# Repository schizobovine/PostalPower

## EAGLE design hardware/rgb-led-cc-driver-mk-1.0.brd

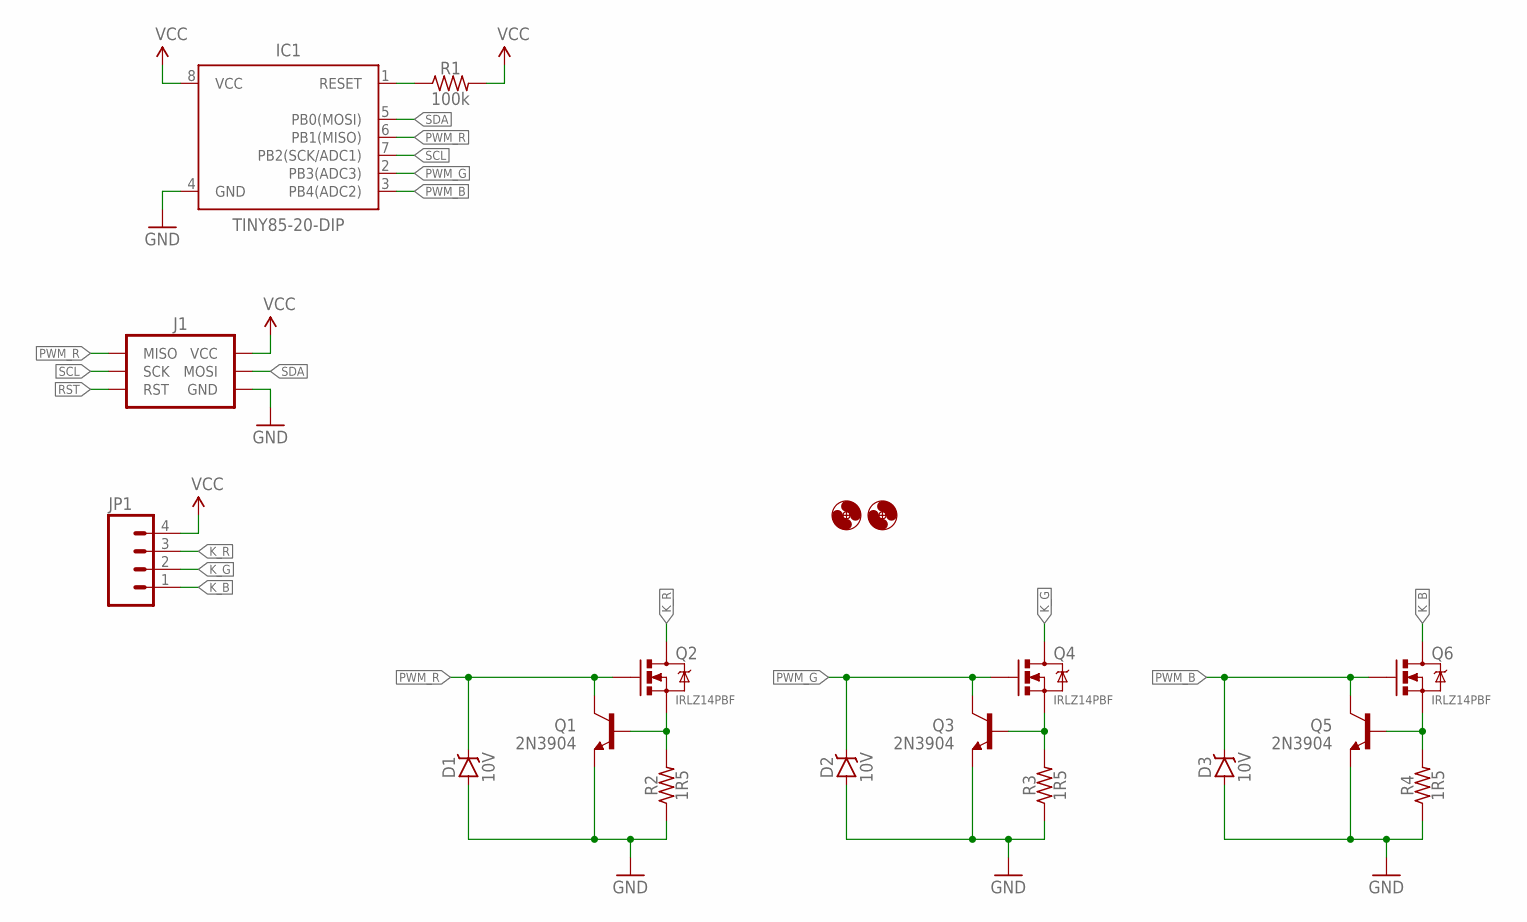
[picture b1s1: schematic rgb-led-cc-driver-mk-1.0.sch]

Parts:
D1, D2, D3: 10V; DIODE-7.62MM
H1, H2: HOLE#2; HOLE-#2
IC1: TINY85-20-DIP; DIP08
J1: AVR_SPI_PRG_6PTH_INLINE_I2C; AVR_ISP_INLINE_PTH_I2C
JP1: M04PTH; 1X04-PTH-VERT
Q1, Q3, Q5: 2N3904; TO-92-AMMO
Q2, Q4, Q6: IRLZ14PBF; TO220-THERMPAD
R1: 100k; RESISTOR-AXIAL-PTH-6.35MM
R2, R3, R4: 1R5; RESISTOR-AXIAL-PTH-10.16MM

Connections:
GND: D1.A, D2.A, D3.A, IC1.4 (GND), J1.GND, Q1.1 (E), Q3.1 (E), Q5.1 (E), R2.P$1 (1), R3.P$1 (1), R4.P$1 (1)
K_B: JP1.1, Q6.2@1 (D), Q6.2@2 (D)
K_G: JP1.2, Q4.2@1 (D), Q4.2@2 (D)
K_R: JP1.3, Q2.2@1 (D), Q2.2@2 (D)
unnamed: Q1.2 (B), Q2.3 (S), R2.P$2 (2)
unnamed: Q3.2 (B), Q4.3 (S), R3.P$2 (2)
unnamed: Q5.2 (B), Q6.3 (S), R4.P$2 (2)
PWM_B: D3.K (C), IC1.3 (PB4(ADC2)), Q5.3 (C), Q6.1 (G)
PWM_G: D2.K (C), IC1.2 (PB3(ADC3)), Q3.3 (C), Q4.1 (G)
PWM_R: D1.K (C), IC1.6 (PB1(MISO)), J1.MISO, Q1.3 (C), Q2.1 (G)
RST: IC1.1 (RESET), J1.RESET (RST), R1.P$1 (1)
SCL: IC1.7 (PB2(SCK/ADC1)), J1.SCK
SDA: IC1.5 (PB0(MOSI)), J1.MOSI
VCC: IC1.8 (VCC), J1.VCC, JP1.4, R1.P$2 (2)

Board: 2 copper layers, 18 parts (0 on the bottom side), 14 nets, no tracks yet.

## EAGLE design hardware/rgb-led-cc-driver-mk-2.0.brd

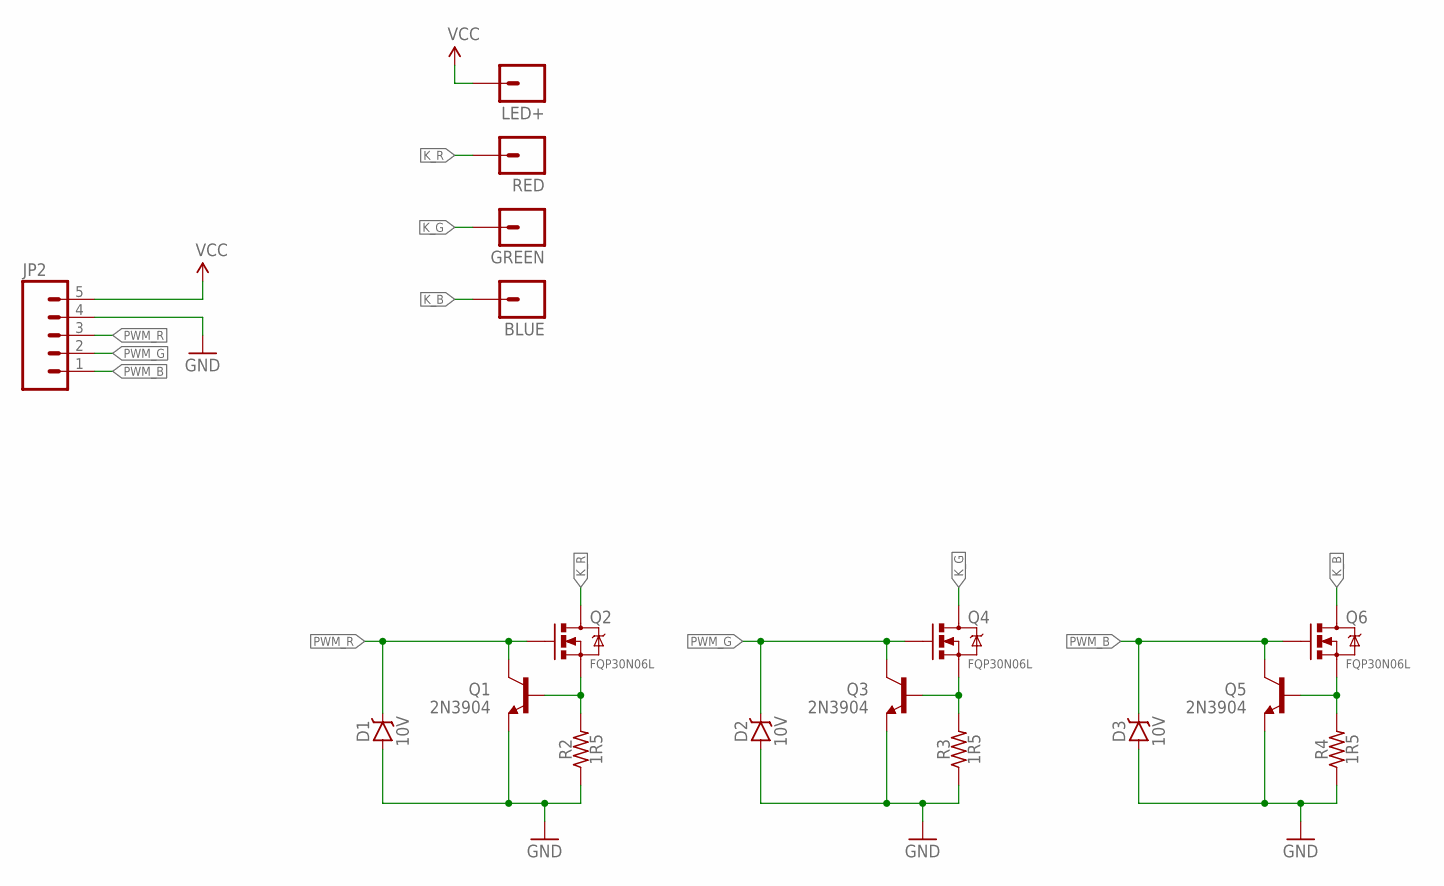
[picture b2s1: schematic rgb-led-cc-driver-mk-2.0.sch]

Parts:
BLUE: M01PTH_2MM; 1X01_2MM
D1, D2, D3: 10V; DIODE-ZENNER-7.62MM
GREEN: M01PTH_2MM; 1X01_2MM
JP2: M05PTH; 1X05
LED+: M01PTH_2MM; 1X01_2MM
Q1, Q3, Q5: 2N3904; TO-92-AMMO
Q2, Q4, Q6: FQP30N06L; TO220-THERMPAD
R2, R3, R4: 1R5; RESISTOR-AXIAL-PTH-10.16MM
RED: M01PTH_2MM; 1X01_2MM

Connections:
GND: D1.A, D2.A, D3.A, JP2.4, Q1.1 (E), Q3.1 (E), Q5.1 (E), R2.P$1 (1), R3.P$1 (1), R4.P$1 (1)
K_B: BLUE.1, Q6.2@1 (D), Q6.2@2 (D)
K_G: GREEN.1, Q4.2@1 (D), Q4.2@2 (D)
K_R: Q2.2@1 (D), Q2.2@2 (D), RED.1
unnamed: Q1.2 (B), Q2.3 (S), R2.P$2 (2)
unnamed: Q3.2 (B), Q4.3 (S), R3.P$2 (2)
unnamed: Q5.2 (B), Q6.3 (S), R4.P$2 (2)
PWM_B: D3.K (C), JP2.1, Q5.3 (C), Q6.1 (G)
PWM_G: D2.K (C), JP2.2, Q3.3 (C), Q4.1 (G)
PWM_R: D1.K (C), JP2.3, Q1.3 (C), Q2.1 (G)
VCC: JP2.5, LED+.1

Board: 2 copper layers, 17 parts (0 on the bottom side), 11 nets, no tracks yet.

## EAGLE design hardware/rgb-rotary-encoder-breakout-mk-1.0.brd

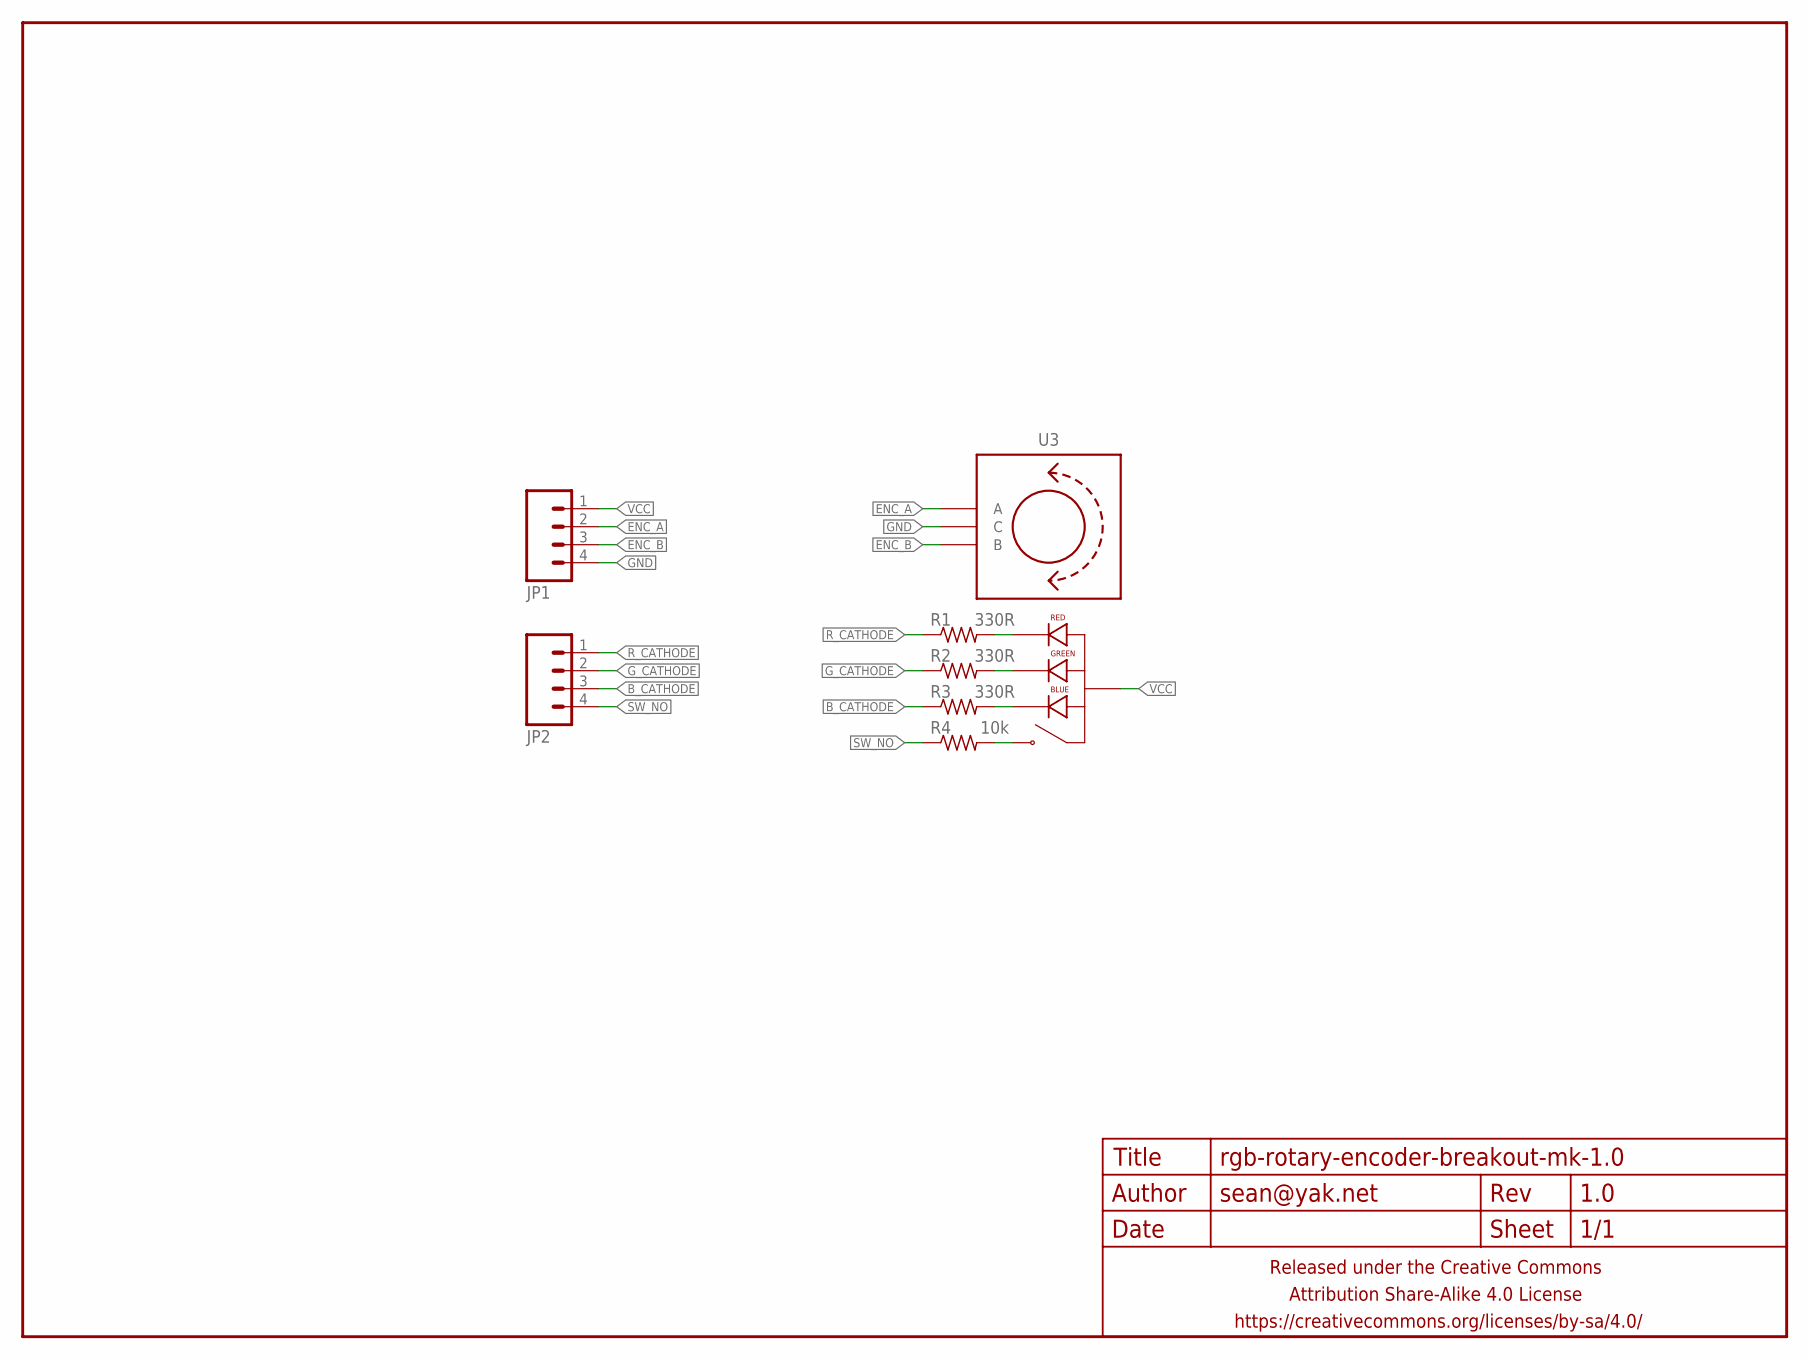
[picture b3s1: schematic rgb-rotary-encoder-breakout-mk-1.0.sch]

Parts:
FRAME1: FRAME-LETTERNO_PACKAGE; DUMMY
JP1, JP2: M04PTH; 1X04-PTH-VERT
R1, R2, R3: 330R; RESISTOR-AXIAL-PTH-7.62MM
R4: 10k; RESISTOR-AXIAL-PTH-7.62MM
U3: ROTARY_ENCODER_SWITCH_RGBNO_LAB_TOP; ROTARY_ENCODER_SWITCH_RGB_NO_LAB_TOP

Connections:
B_CATHODE: JP2.3, R3.P$1 (1)
ENC_A: JP1.2, U3.ENC_A (A)
ENC_B: JP1.3, U3.ENC_B (B)
GND: JP1.4, U3.ENC_COM (C)
G_CATHODE: JP2.2, R2.P$1 (1)
unnamed: R4.P$2 (2), U3.SW_NO (NO)
unnamed: R1.P$2 (2), U3.LED_R (RED_CATHODE)
unnamed: R2.P$2 (2), U3.LED_G (GREEN_CATHODE)
unnamed: R3.P$2 (2), U3.LED_B (BLUE_CATHODE)
R_CATHODE: JP2.1, R1.P$1 (1)
SW_NO: JP2.4, R4.P$1 (1)
VCC: JP1.1, U3.LED_SW_COM (ANODE)

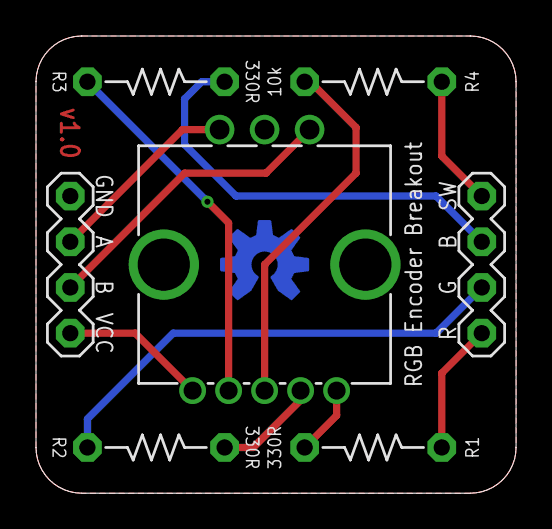
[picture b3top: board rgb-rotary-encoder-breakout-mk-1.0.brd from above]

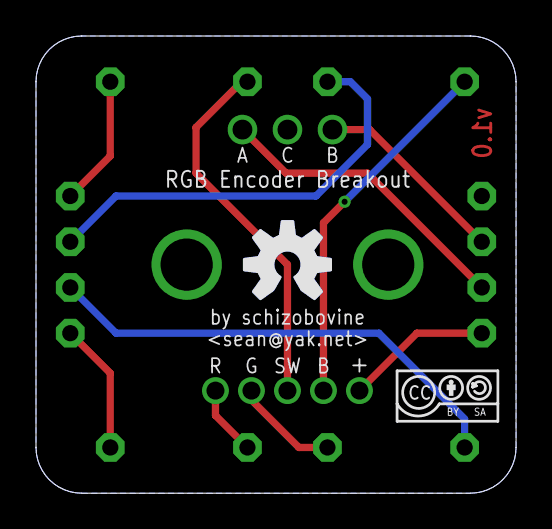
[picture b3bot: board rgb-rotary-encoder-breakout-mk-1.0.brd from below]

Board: 2 copper layers, 26.7 x 25.4 mm, 10 parts (2 on the bottom side), 12 nets.

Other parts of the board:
U$1: OSHWLOGO_5MM_METAL
U$2: CC-BY-SA-4.0-NO-URL

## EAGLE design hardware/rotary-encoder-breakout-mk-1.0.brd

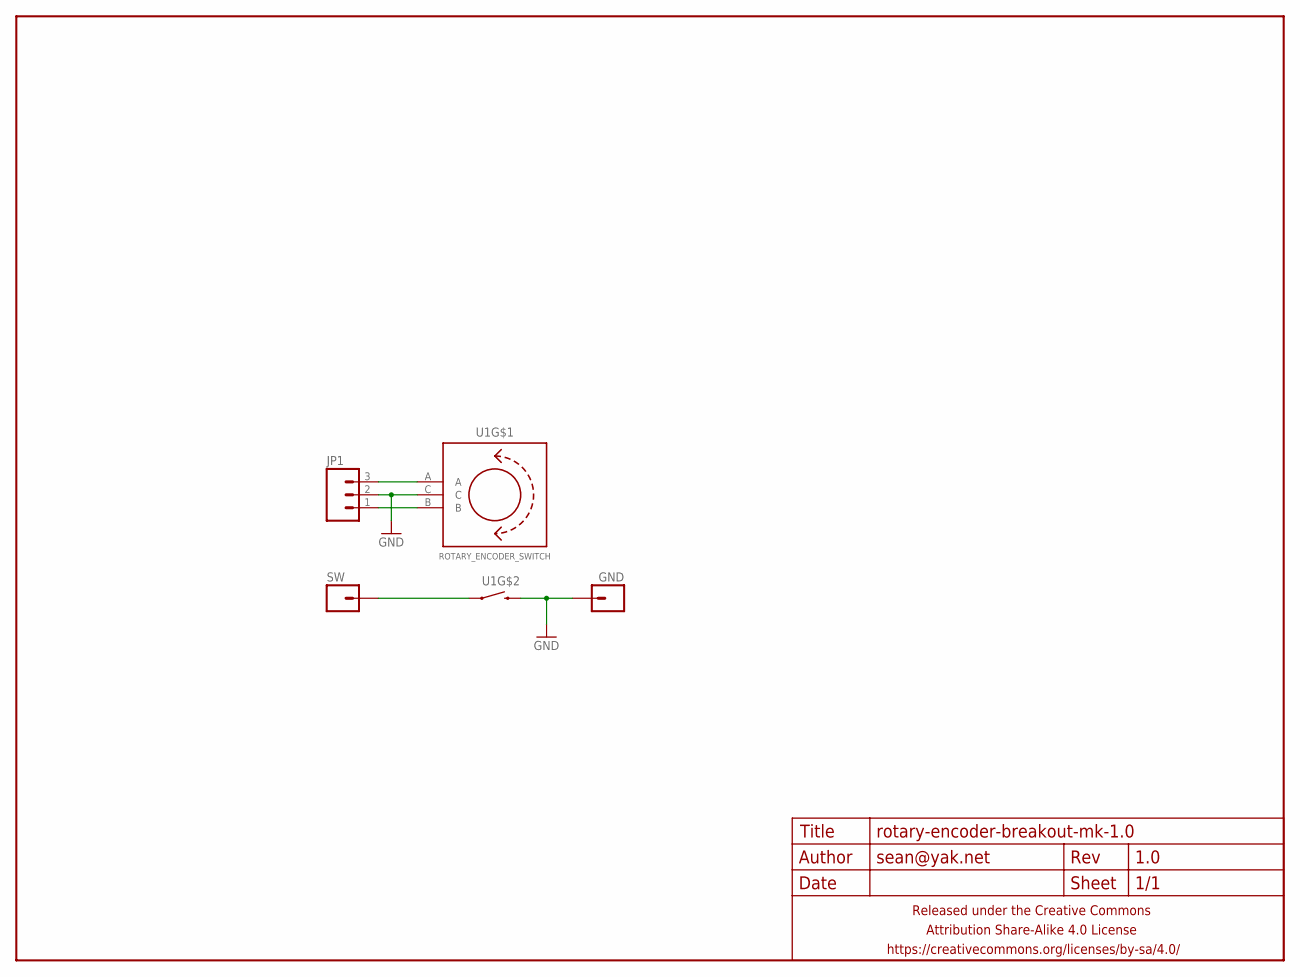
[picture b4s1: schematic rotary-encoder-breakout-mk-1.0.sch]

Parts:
FRAME1: FRAME-LETTERNO_PACKAGE; DUMMY
GND: M01PTH; 1X01
JP1: M03PTH; 1X03
SW: M01PTH; 1X01
U1: ROTARY_ENCODER_SWITCH

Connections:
GND: GND.1, JP1.2, U1.C, U1.SW2 (2)
unnamed: JP1.3, U1.A
unnamed: JP1.1, U1.B
SW1: SW.1, U1.SW1 (1)

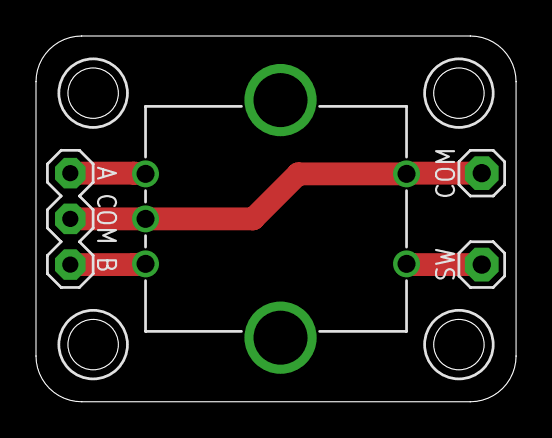
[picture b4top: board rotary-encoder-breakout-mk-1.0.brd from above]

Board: 2 copper layers, 26.7 x 20.3 mm, 5 parts (0 on the bottom side), 4 nets.

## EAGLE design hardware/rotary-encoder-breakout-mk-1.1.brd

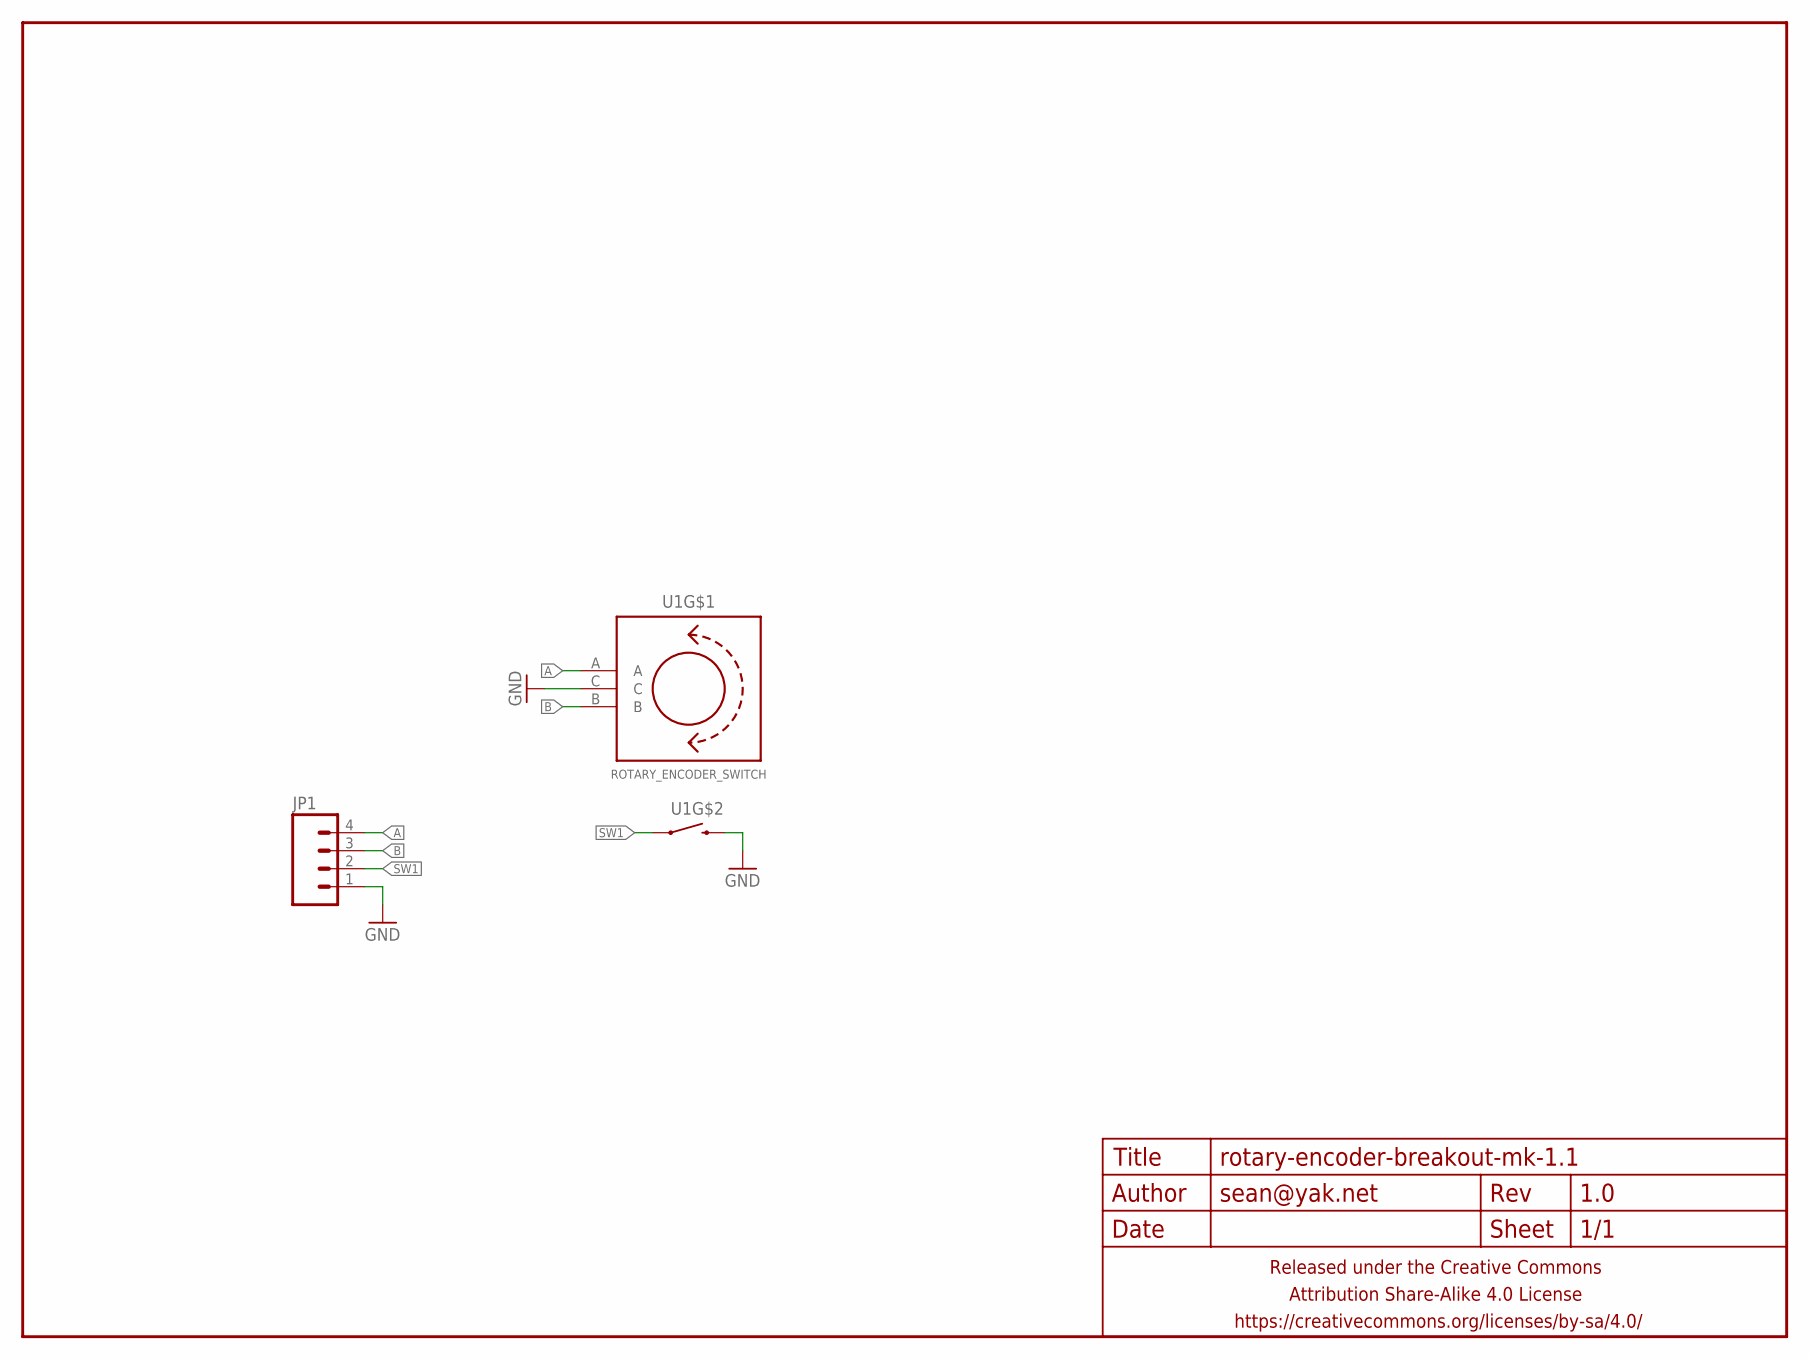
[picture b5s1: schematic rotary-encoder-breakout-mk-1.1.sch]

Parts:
FRAME1: FRAME-LETTERNO_PACKAGE; DUMMY
JP1: M04PTH; 1X04-PTH-VERT
U1: ROTARY_ENCODER_SWITCH

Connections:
A: JP1.4, U1.A
B: JP1.3, U1.B
GND: JP1.1, U1.C, U1.SW2 (2)
SW1: JP1.2, U1.SW1 (1)

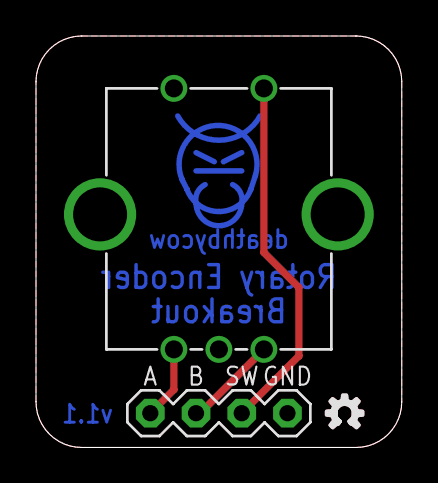
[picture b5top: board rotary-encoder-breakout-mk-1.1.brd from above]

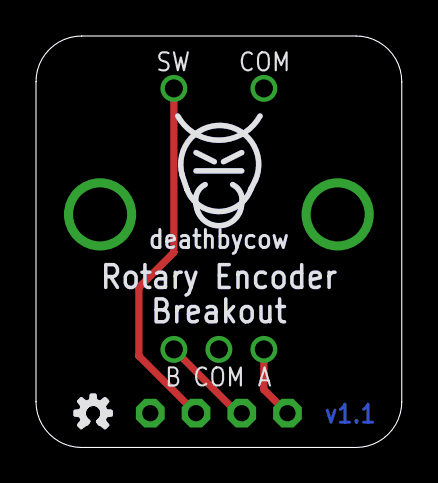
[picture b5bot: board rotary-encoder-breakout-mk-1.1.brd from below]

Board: 2 copper layers, 20.3 x 22.9 mm, 6 parts (2 on the bottom side), 4 nets.

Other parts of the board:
U$1, U$3: OSHWLOGO_TINY
U$2: COW_SMALL_METAL

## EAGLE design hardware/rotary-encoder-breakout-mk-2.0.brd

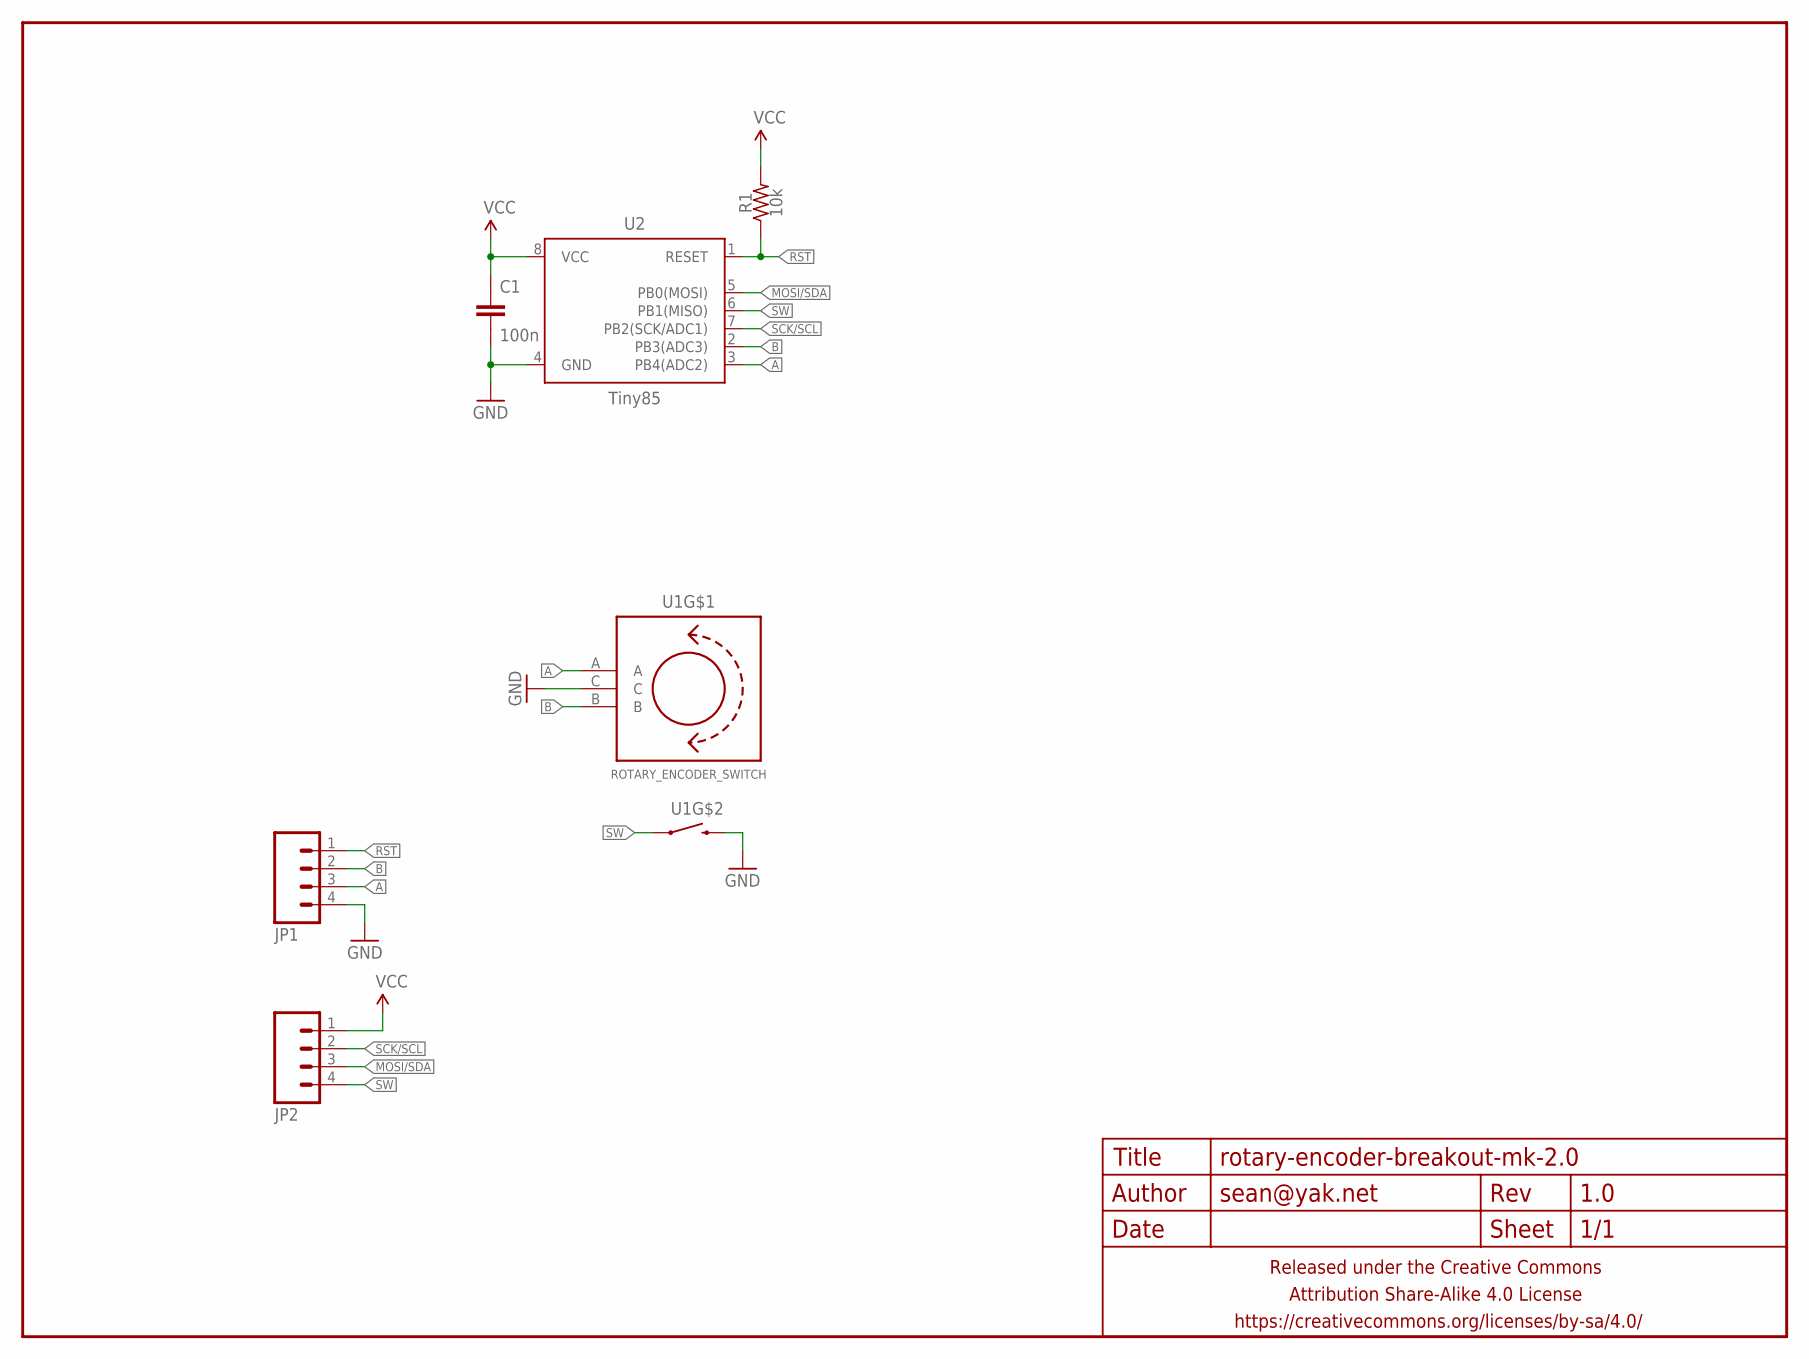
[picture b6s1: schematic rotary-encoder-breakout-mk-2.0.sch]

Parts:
C1: 100n; C0805
FRAME1: FRAME-LETTERNO_PACKAGE; DUMMY
JP1, JP2: M04PTH; 1X04-PTH-VERT
R1: 10k; R0805
U1: ROTARY_ENCODER_SWITCH
U2: Tiny85; SO08-EIAJ

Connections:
A: JP1.3, U1.A, U2.3 (PB4(ADC2))
B: JP1.2, U1.B, U2.2 (PB3(ADC3))
GND: C1.2, JP1.4, U1.C, U1.SW2 (2), U2.4 (GND)
MOSI/SDA: JP2.3, U2.5 (PB0(MOSI))
RST: JP1.1, R1.1, U2.1 (RESET)
SCK/SCL: JP2.2, U2.7 (PB2(SCK/ADC1))
SW: JP2.4, U1.SW1 (1), U2.6 (PB1(MISO))
VCC: C1.1, JP2.1, R1.2, U2.8 (VCC)

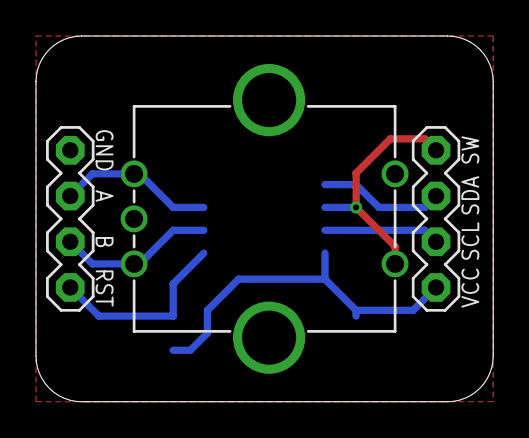
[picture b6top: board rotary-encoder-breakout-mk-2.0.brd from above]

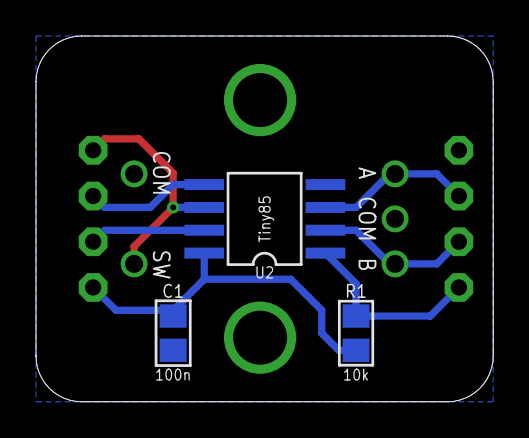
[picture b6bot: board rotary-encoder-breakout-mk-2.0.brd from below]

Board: 2 copper layers, 25.4 x 20.3 mm, 7 parts (3 on the bottom side), 8 nets.

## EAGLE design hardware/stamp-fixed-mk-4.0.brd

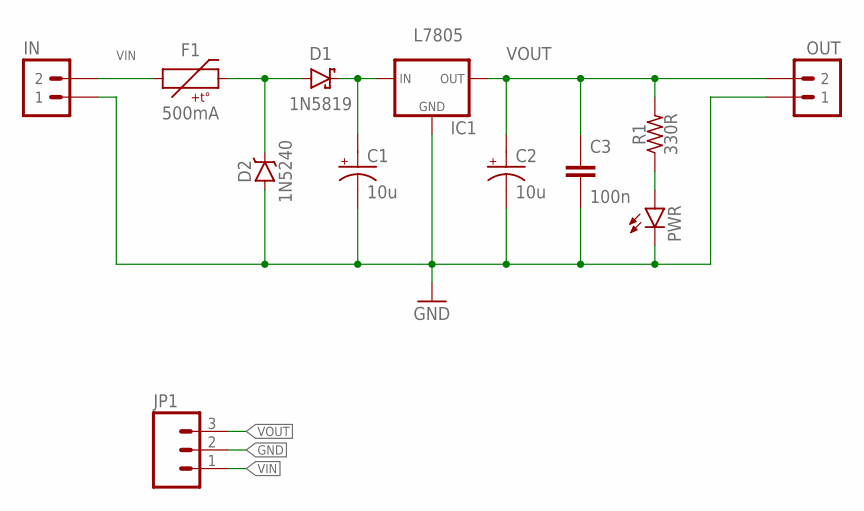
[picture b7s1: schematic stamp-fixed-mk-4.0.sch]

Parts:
C1, C2: 10u; E2,5-5
C3: 100n; C025-024X044
D1: 1N5819; DIODE-SCHOTTKY-10.16MM
D2: 1N5240; DIODE-ZENNER-10.16MM
F1: 500mA; PTC-PTH-5.08MM
IC1: L7805; TO220-IGO-THERMPAD
IN: M02PTH-CENTERED-R+; 1X02-CENTER-R+
JP1: M03PTH-CENTERED; 1X03-CENTERED
OUT: M02PTH-CENTERED-R+; 1X02-CENTER-R+
PWR: LED3MM-LESS; LED3MM-LESSSILK
R1: 330R; RESISTOR-AXIAL-PTH-5.08MM

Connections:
GND: C1.-, C2.-, C3.2, D2.A, IC1.4 (GND), IC1.GND, IN.1, JP1.2, OUT.1, PWR.K (C)
unnamed: PWR.A, R1.P$1 (1)
unnamed: C1.+, D1.C, IC1.IN
unnamed: D1.A, D2.K (C), F1.P$2 (2)
VIN: F1.P$1 (1), IN.2, JP1.1
VOUT: C2.+, C3.1, IC1.OUT, JP1.3, OUT.2, R1.P$2 (2)

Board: 2 copper layers, 12 parts (0 on the bottom side), 6 nets, no tracks yet.

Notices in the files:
parts and their libraries:
A_butts: Released under the Creative Commons Attribution Share-Alike 4.0 License
A_butts: https://creativecommons.org/licenses/by-sa/4.0
A_butts: Released under the Creative Commons
